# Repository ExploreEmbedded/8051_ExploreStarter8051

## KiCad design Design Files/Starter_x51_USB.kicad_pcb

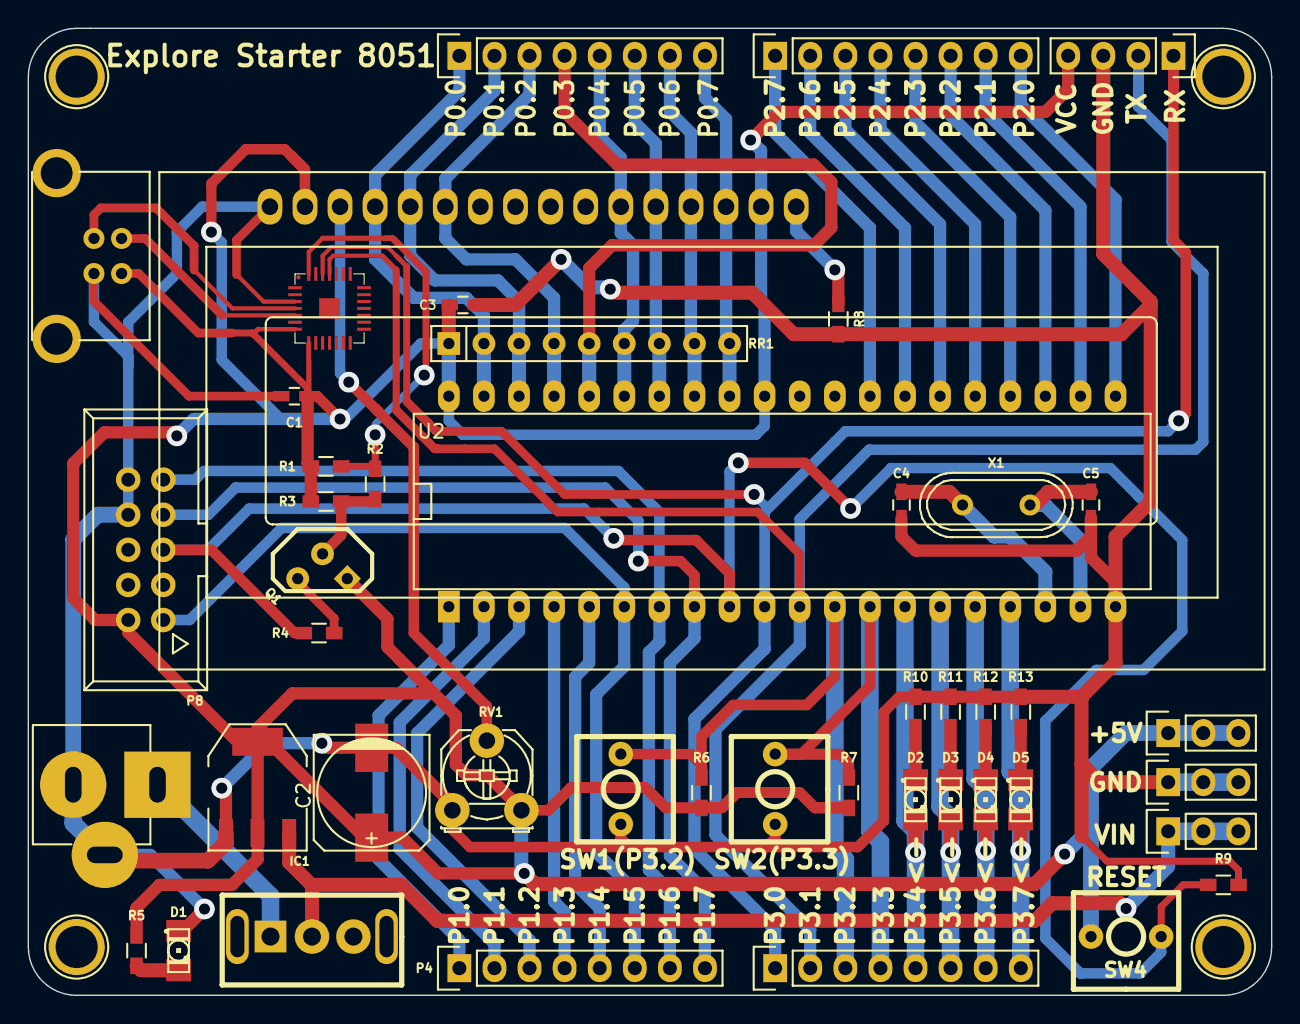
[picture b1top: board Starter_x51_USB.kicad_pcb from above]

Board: 2 copper layers, 90.0 x 70.0 mm, 50 parts (0 on the bottom side), 51 nets.

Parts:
C1, C3: 0.1uF; C_0603_HandSoldering
C2: 100uF,25v; c_elec_8x10.5
C4: 22pF; C_0603_HandSoldering
C5: 22Pf; C_0603_HandSoldering
CON1: BARREL_JACK; JACK_ALIM
CON2: USB-MINI-B; USB_B
D1, D2, D3, D4, D5: LED; LED-1206_NEW
DS1: LCD-016N002L; WC1602A
IC1: LM1117; LM_1117
P1, P2, P3: CONN_01X03; Pin_Header_Straight_1x03
P4, P5, P6, P7: CONN_01X08; Pin_Header_Straight_1x08
P8: CONN_02X05; VASCH5x2
P9, P10, P11, P12: CONN_01X01; 1pin
P13: CONN_01X04; Pin_Header_Straight_1x04
Q1: PNP; BC557
R1, R3, R8: 1k; R_0603_HandSoldering
R2: 4.7k; R_0603_HandSoldering
R4: 100r; R_0603_HandSoldering
R5, R10, R11, R12, R13: 470r; R_0603_HandSoldering
R6, R7: R; R_0603_HandSoldering
R9: 10k; R_0603_HandSoldering
RR1: RR8; Resistor_Array_SIP8
RV1: POT; Potentiometer_Triwood_RM-065
SW1: SW_PUSH; SPSPT_XL_NEW
SW2, SW3, SW4: SW_PUSH; SW_PUSH_SMALL_2pin_3D_xl
U1: CP2102; cp2102_xl2
U2: AT89S52; DIP-40__600_ELL
X1: CRYSTAL; Crystal_HC49-U_Vertical

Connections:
/D4: DS1.11, P7.5, RR1.6, U2.35
/D5: DS1.12, P7.6, RR1.7, U2.34
/D6: DS1.13, P7.7, RR1.8, U2.33
/D7: DS1.14, P7.8, RR1.9, U2.32
/DTR: R1.1, R2.2, U1.28
/E: DS1.6, P7.3, RR1.4, U2.37
/L1: D2.1, P5.5, U2.14
/L2: D3.1, P5.6, U2.15
/L3: D4.1, P5.7, U2.16
/L4: D5.1, P5.8, U2.17
/MISO: P4.7, P8.9, U2.7
/MOSI: P4.6, P8.1, U2.6
/R/W: DS1.5, P7.2, RR1.3, U2.38
/RS: DS1.4, P7.1, RR1.2, U2.39
/RST: P8.5, R4.1, R9.1, SW4.1, U2.9
/RX: P5.1, P13.1, U1.26, U2.10
/SCK: P4.8, P8.7, U2.8
/SW1: P5.3, R6.1, SW2.1, U2.12
/SW2: P5.4, R7.1, SW3.1, U2.13
/TX: P5.2, P13.2, U1.25, U2.11
/Vin: IC1.3, P1.1, P1.2, P1.3, SW1.2
GND: C1.2, C2.2, C3.2, C4.2, C5.2, CON1.2, CON1.3, CON2.4, D1.2, DS1.1, IC1.1, P2.1, P2.2, P2.3, P8.8, P8.10, P13.3, R8.2, R9.2, R10.1, R11.1, R12.1, R13.1, RV1.1, SW2.2, SW3.2, U1.3, U2.20
unnamed: C4.1, U2.18, X1.1
unnamed: C5.1, U2.19, X1.2
unnamed: CON1.1, SW1.1
unnamed: CON2.2, U1.5
unnamed: CON2.3, U1.4
unnamed: D1.1, R5.1
unnamed: D2.2, R10.2
unnamed: D3.2, R11.2
unnamed: D4.2, R12.2
unnamed: D5.2, R13.2
unnamed: DS1.3, RV1.2
unnamed: DS1.16, R8.1
unnamed: P4.1, U2.1
unnamed: P4.2, U2.2
unnamed: P4.3, U2.3
unnamed: P4.4, U2.4
unnamed: P4.5, U2.5
unnamed: P6.1, U2.28
unnamed: P6.2, U2.27
unnamed: P6.3, U2.26
unnamed: P6.4, U2.25
unnamed: P6.5, U2.24
unnamed: P6.6, U2.23
unnamed: P6.7, U2.22
unnamed: P6.8, U2.21
unnamed: P7.4, RR1.5, U2.36
unnamed: Q1.2, R2.1, R3.2
unnamed: Q1.3, R4.2
VCC: C1.1, C2.1, C3.1, CON2.1, DS1.2, DS1.15, IC1.2, IC1.4, P3.1, P3.2, P3.3, P8.2, P13.4, Q1.1, R1.2, R3.1, R5.2, R6.2, R7.2, RR1.1, RV1.3, SW4.2, U1.7, U1.8, U2.31, U2.40

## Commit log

2016-03-23 Added design Files
2016-05-03 Added Sample Code
    Added Sample code for 8051
    IDE:Keil
2016-06-15 LED blink code added
2016-06-20 Switch LED code updated
2016-06-20 LCD code updated
2017-07-12 BOM Generated
2017-09-23 Added the glcd example with libraries
